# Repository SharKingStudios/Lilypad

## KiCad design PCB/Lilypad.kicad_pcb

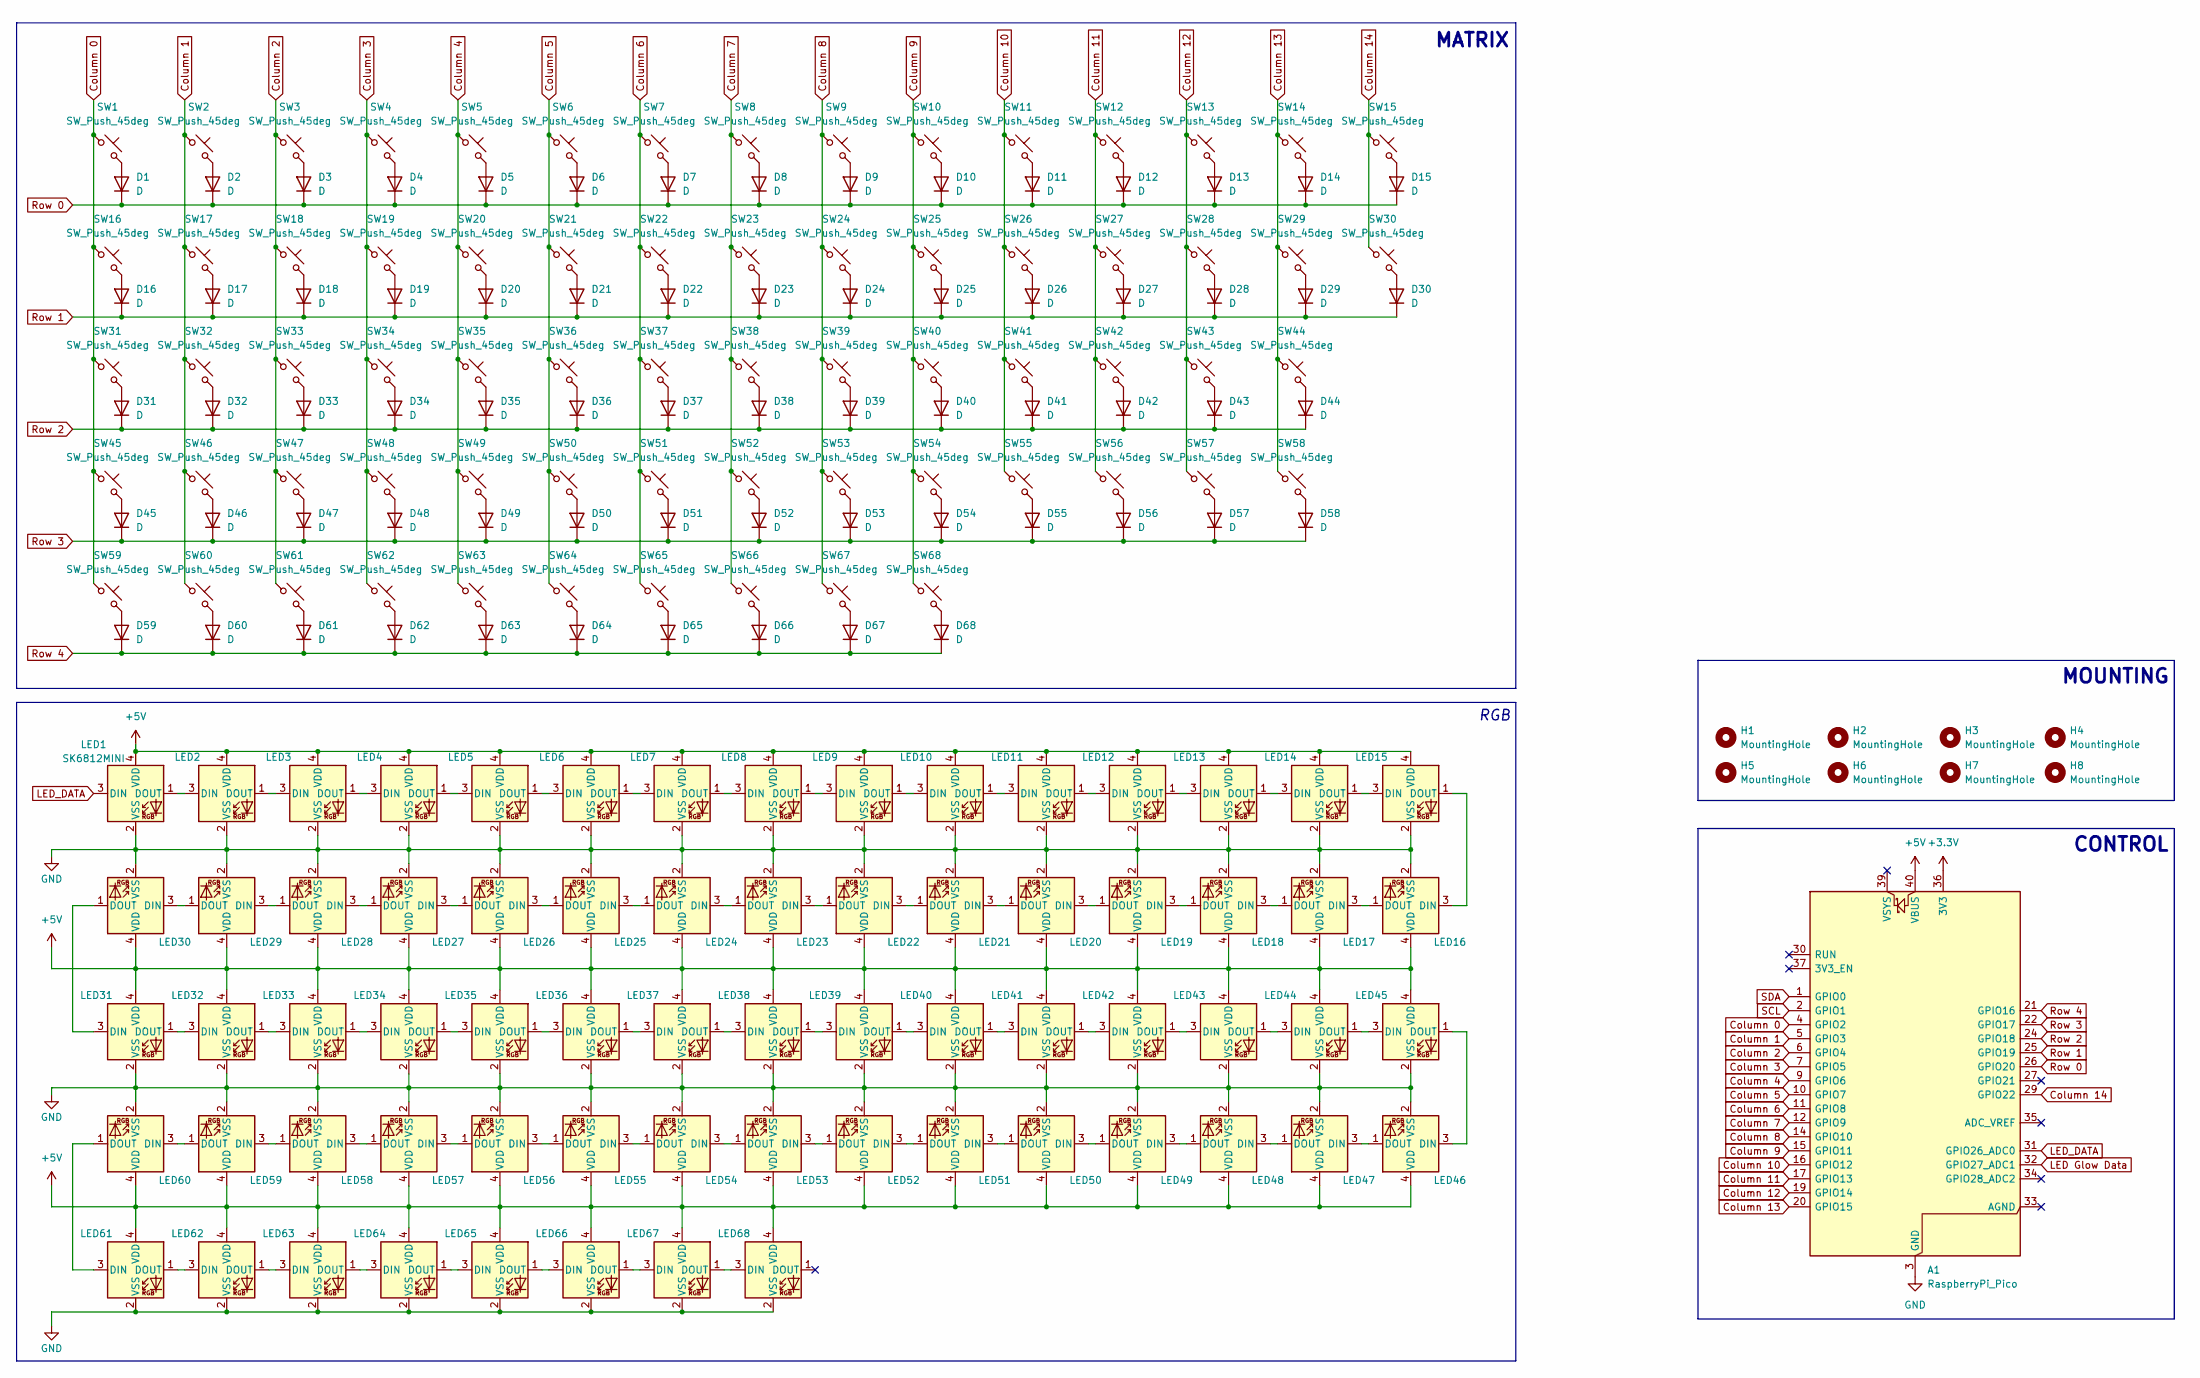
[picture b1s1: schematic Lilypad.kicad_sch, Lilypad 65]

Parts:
A1: RaspberryPi_Pico; RaspberryPi_Pico_Common_Unspecified
D1, D2, D3, D4, D5, D6, D7, D8, D9, D10, D11, D12, D13, D14, D15, D16, D17, D18, D19, D20, D21, D22, D23, D24, D25, D26, D27, D28, D29, D30, D31, D32, D33, D34, D35, D36, D37, D38, D39, D40, D41, D42, D43, D44, D45, D46, D47, D48, D49, D50, D51, D52, D53, D54, D55, D56, D57, D58, D59, D60, D61, D62, D63, D64, D65, D66, D67, D68: D; D_SOD-123F
H1, H2, H3, H4, H5, H6, H7, H8: MountingHole; MountingHole_3.2mm_M3_Pad_Via
LED1, LED2, LED3, LED4, LED5, LED6, LED7, LED8, LED9, LED10, LED11, LED12, LED13, LED14, LED15, LED16, LED17, LED18, LED19, LED20, LED21, LED22, LED23, LED24, LED25, LED26, LED27, LED28, LED29, LED30, LED31, LED32, LED33, LED34, LED35, LED36, LED37, LED38, LED39, LED40, LED41, LED42, LED43, LED44, LED45, LED46, LED47, LED48, LED49, LED50, LED51, LED52, LED53, LED54, LED55, LED56, LED57, LED58, LED59, LED60, LED61, LED62, LED63, LED64, LED65, LED66, LED67, LED68: SK6812MINI; SK6812-MINI-E
SW1, SW2, SW3, SW4, SW5, SW6, SW7, SW8, SW9, SW10, SW11, SW12, SW13, SW14, SW15, SW16, SW17, SW18, SW19, SW20, SW21, SW22, SW23, SW24, SW25, SW26, SW27, SW28, SW29, SW30, SW31, SW32, SW33, SW34, SW35, SW36, SW37, SW38, SW39, SW40, SW41, SW42, SW43, SW44, SW45, SW46, SW47, SW48, SW49, SW50, SW51, SW52, SW53, SW54, SW55, SW56, SW57, SW58, SW59, SW60, SW61, SW62, SW63, SW64, SW65, SW66, SW67, SW68: SW_Push_45deg; Kailh-PG1353-Hotswap-1U

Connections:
+3.3V: A1.36 (3V3)
+5V: A1.40 (VBUS), LED1.4 (VDD), LED2.4 (VDD), LED3.4 (VDD), LED4.4 (VDD), LED5.4 (VDD), LED6.4 (VDD), LED7.4 (VDD), LED8.4 (VDD), LED9.4 (VDD), LED10.4 (VDD), LED11.4 (VDD), LED12.4 (VDD), LED13.4 (VDD), LED14.4 (VDD), LED15.4 (VDD), LED16.4 (VDD), LED17.4 (VDD), LED18.4 (VDD), LED19.4 (VDD), LED20.4 (VDD), LED21.4 (VDD), LED22.4 (VDD), LED23.4 (VDD), LED24.4 (VDD), LED25.4 (VDD), LED26.4 (VDD), LED27.4 (VDD), LED28.4 (VDD), LED29.4 (VDD), LED30.4 (VDD), LED31.4 (VDD), LED32.4 (VDD), LED33.4 (VDD), LED34.4 (VDD), LED35.4 (VDD), LED36.4 (VDD), LED37.4 (VDD), LED38.4 (VDD), LED39.4 (VDD), LED40.4 (VDD), LED41.4 (VDD), LED42.4 (VDD), LED43.4 (VDD), LED44.4 (VDD), LED45.4 (VDD), LED46.4 (VDD), LED47.4 (VDD), LED48.4 (VDD), LED49.4 (VDD), LED50.4 (VDD), LED51.4 (VDD), LED52.4 (VDD), LED53.4 (VDD), LED54.4 (VDD), LED55.4 (VDD), LED56.4 (VDD), LED57.4 (VDD), LED58.4 (VDD), LED59.4 (VDD), LED60.4 (VDD), LED61.4 (VDD), LED62.4 (VDD), LED63.4 (VDD), LED64.4 (VDD), LED65.4 (VDD), LED66.4 (VDD), LED67.4 (VDD), LED68.4 (VDD)
Column 0: A1.4 (GPIO2), SW1.1, SW16.1, SW31.1, SW45.1, SW59.1
Column 1: A1.5 (GPIO3), SW2.1, SW17.1, SW32.1, SW46.1, SW60.1
Column 2: A1.6 (GPIO4), SW3.1, SW18.1, SW33.1, SW47.1, SW61.1; also elsewhere on the board
Column 3: A1.7 (GPIO5), SW4.1, SW19.1, SW34.1, SW48.1, SW62.1
Column 4: A1.9 (GPIO6), SW5.1, SW20.1, SW35.1, SW49.1, SW63.1
Column 5: A1.10 (GPIO7), SW6.1, SW21.1, SW36.1, SW50.1, SW64.1
Column 6: A1.11 (GPIO8), SW7.1, SW22.1, SW37.1, SW51.1, SW65.1
Column 7: A1.12 (GPIO9), SW8.1, SW23.1, SW38.1, SW52.1, SW66.1
Column 8: A1.14 (GPIO10), SW9.1, SW24.1, SW39.1, SW53.1, SW67.1
Column 9: A1.15 (GPIO11), SW10.1, SW25.1, SW40.1, SW54.1, SW68.1
Column 10: A1.16 (GPIO12), SW11.1, SW26.1, SW41.1, SW55.1
Column 11: A1.17 (GPIO13), SW12.1, SW27.1, SW42.1, SW56.1
Column 12: A1.19 (GPIO14), SW13.1, SW28.1, SW43.1, SW57.1
Column 13: A1.20 (GPIO15), SW14.1, SW29.1, SW44.1, SW58.1
Column 14: A1.29 (GPIO22), SW15.1, SW30.1
GND: A1.3 (GND), A1.8 (GND), A1.13 (GND), A1.18 (GND), A1.23 (GND), A1.28 (GND), A1.38 (GND), LED1.2 (VSS), LED2.2 (VSS), LED3.2 (VSS), LED4.2 (VSS), LED5.2 (VSS), LED6.2 (VSS), LED7.2 (VSS), LED8.2 (VSS), LED9.2 (VSS), LED10.2 (VSS), LED11.2 (VSS), LED12.2 (VSS), LED13.2 (VSS), LED14.2 (VSS), LED15.2 (VSS), LED16.2 (VSS), LED17.2 (VSS), LED18.2 (VSS), LED19.2 (VSS), LED20.2 (VSS), LED21.2 (VSS), LED22.2 (VSS), LED23.2 (VSS), LED24.2 (VSS), LED25.2 (VSS), LED26.2 (VSS), LED27.2 (VSS), LED28.2 (VSS), LED29.2 (VSS), LED30.2 (VSS), LED31.2 (VSS), LED32.2 (VSS), LED33.2 (VSS), LED34.2 (VSS), LED35.2 (VSS), LED36.2 (VSS), LED37.2 (VSS), LED38.2 (VSS), LED39.2 (VSS), LED40.2 (VSS), LED41.2 (VSS), LED42.2 (VSS), LED43.2 (VSS), LED44.2 (VSS), LED45.2 (VSS), LED46.2 (VSS), LED47.2 (VSS), LED48.2 (VSS), LED49.2 (VSS), LED50.2 (VSS), LED51.2 (VSS), LED52.2 (VSS), LED53.2 (VSS), LED54.2 (VSS), LED55.2 (VSS), LED56.2 (VSS), LED57.2 (VSS), LED58.2 (VSS), LED59.2 (VSS), LED60.2 (VSS), LED61.2 (VSS), LED62.2 (VSS), LED63.2 (VSS), LED64.2 (VSS), LED65.2 (VSS), LED66.2 (VSS), LED67.2 (VSS), LED68.2 (VSS)
LED Glow Data: A1.32 (GPIO27_ADC1)
LED_DATA: A1.31 (GPIO26_ADC0), LED1.3 (DIN)
unnamed: D1.2 (A), SW1.2
unnamed: D2.2 (A), SW2.2
unnamed: D3.2 (A), SW3.2
unnamed: D4.2 (A), SW4.2
unnamed: D5.2 (A), SW5.2
unnamed: D6.2 (A), SW6.2
unnamed: D7.2 (A), SW7.2
unnamed: D8.2 (A), SW8.2
unnamed: D9.2 (A), SW9.2
unnamed: D10.2 (A), SW10.2
unnamed: D11.2 (A), SW11.2
unnamed: D12.2 (A), SW12.2
unnamed: D13.2 (A), SW13.2
unnamed: D14.2 (A), SW14.2
unnamed: D15.2 (A), SW15.2
unnamed: D16.2 (A), SW16.2
unnamed: D17.2 (A), SW17.2
unnamed: D18.2 (A), SW18.2
unnamed: D19.2 (A), SW19.2
unnamed: D20.2 (A), SW20.2
unnamed: D21.2 (A), SW21.2
unnamed: D22.2 (A), SW22.2
unnamed: D23.2 (A), SW23.2
unnamed: D24.2 (A), SW24.2
unnamed: D25.2 (A), SW25.2
unnamed: D26.2 (A), SW26.2
unnamed: D27.2 (A), SW27.2
unnamed: D28.2 (A), SW28.2
unnamed: D29.2 (A), SW29.2
unnamed: D30.2 (A), SW30.2
unnamed: D31.2 (A), SW31.2
unnamed: D32.2 (A), SW32.2
unnamed: D33.2 (A), SW33.2
unnamed: D34.2 (A), SW34.2
unnamed: D35.2 (A), SW35.2
unnamed: D36.2 (A), SW36.2
unnamed: D37.2 (A), SW37.2
unnamed: D38.2 (A), SW38.2
unnamed: D39.2 (A), SW39.2
unnamed: D40.2 (A), SW40.2
unnamed: D41.2 (A), SW41.2
unnamed: D42.2 (A), SW42.2
unnamed: D43.2 (A), SW43.2
unnamed: D44.2 (A), SW44.2
unnamed: D45.2 (A), SW45.2
unnamed: D46.2 (A), SW46.2
unnamed 66: D47.2 (A), SW47.2; also elsewhere on the board
unnamed: D48.2 (A), SW48.2
unnamed: D49.2 (A), SW49.2
unnamed: D50.2 (A), SW50.2
unnamed: D51.2 (A), SW51.2
unnamed: D52.2 (A), SW52.2
unnamed: D53.2 (A), SW53.2
unnamed: D54.2 (A), SW54.2
unnamed: D55.2 (A), SW55.2
unnamed: D56.2 (A), SW56.2
unnamed: D57.2 (A), SW57.2
unnamed: D58.2 (A), SW58.2
unnamed: D59.2 (A), SW59.2
unnamed: D60.2 (A), SW60.2
unnamed: D61.2 (A), SW61.2
unnamed: D62.2 (A), SW62.2
unnamed: D63.2 (A), SW63.2
unnamed: D64.2 (A), SW64.2
unnamed: D65.2 (A), SW65.2
unnamed: D66.2 (A), SW66.2
unnamed: D67.2 (A), SW67.2
unnamed: D68.2 (A), SW68.2
unnamed: LED1.1 (DOUT), LED2.3 (DIN)
unnamed: LED2.1 (DOUT), LED3.3 (DIN)
unnamed: LED3.1 (DOUT), LED4.3 (DIN)
unnamed: LED4.1 (DOUT), LED5.3 (DIN)
unnamed: LED5.1 (DOUT), LED6.3 (DIN)
unnamed: LED6.1 (DOUT), LED7.3 (DIN)
unnamed: LED7.1 (DOUT), LED8.3 (DIN)
unnamed: LED8.1 (DOUT), LED9.3 (DIN)
unnamed: LED9.1 (DOUT), LED10.3 (DIN)
unnamed: LED10.1 (DOUT), LED11.3 (DIN)
unnamed: LED11.1 (DOUT), LED12.3 (DIN)
unnamed: LED12.1 (DOUT), LED13.3 (DIN)
unnamed: LED13.1 (DOUT), LED14.3 (DIN)
unnamed: LED14.1 (DOUT), LED15.3 (DIN)
unnamed: LED15.1 (DOUT), LED16.3 (DIN)
unnamed: LED16.1 (DOUT), LED17.3 (DIN)
unnamed: LED17.1 (DOUT), LED18.3 (DIN)
unnamed: LED18.1 (DOUT), LED19.3 (DIN)
unnamed: LED19.1 (DOUT), LED20.3 (DIN)
unnamed: LED20.1 (DOUT), LED21.3 (DIN)
unnamed: LED21.1 (DOUT), LED22.3 (DIN)
unnamed: LED22.1 (DOUT), LED23.3 (DIN)
unnamed: LED23.1 (DOUT), LED24.3 (DIN)
unnamed: LED24.1 (DOUT), LED25.3 (DIN)
unnamed: LED25.1 (DOUT), LED26.3 (DIN)
unnamed: LED26.1 (DOUT), LED27.3 (DIN)
unnamed: LED27.1 (DOUT), LED28.3 (DIN)
unnamed: LED28.1 (DOUT), LED29.3 (DIN)
unnamed: LED29.1 (DOUT), LED30.3 (DIN)
unnamed: LED30.1 (DOUT), LED31.3 (DIN)
unnamed: LED31.1 (DOUT), LED32.3 (DIN)
unnamed: LED32.1 (DOUT), LED33.3 (DIN)
unnamed: LED33.1 (DOUT), LED34.3 (DIN)
unnamed: LED34.1 (DOUT), LED35.3 (DIN)
unnamed: LED35.1 (DOUT), LED36.3 (DIN)
unnamed: LED36.1 (DOUT), LED37.3 (DIN)
unnamed: LED37.1 (DOUT), LED38.3 (DIN)
unnamed: LED38.1 (DOUT), LED39.3 (DIN)
unnamed: LED39.1 (DOUT), LED40.3 (DIN)
unnamed: LED40.1 (DOUT), LED41.3 (DIN)
unnamed: LED41.1 (DOUT), LED42.3 (DIN)
unnamed: LED42.1 (DOUT), LED43.3 (DIN)
unnamed: LED43.1 (DOUT), LED44.3 (DIN)
unnamed: LED44.1 (DOUT), LED45.3 (DIN)
unnamed: LED45.1 (DOUT), LED46.3 (DIN)
unnamed: LED46.1 (DOUT), LED47.3 (DIN)
unnamed: LED47.1 (DOUT), LED48.3 (DIN)
unnamed: LED48.1 (DOUT), LED49.3 (DIN)
unnamed: LED49.1 (DOUT), LED50.3 (DIN)
unnamed: LED50.1 (DOUT), LED51.3 (DIN)
unnamed: LED51.1 (DOUT), LED52.3 (DIN)
unnamed: LED52.1 (DOUT), LED53.3 (DIN)
unnamed: LED53.1 (DOUT), LED54.3 (DIN)
unnamed: LED54.1 (DOUT), LED55.3 (DIN)
unnamed: LED55.1 (DOUT), LED56.3 (DIN)
unnamed: LED56.1 (DOUT), LED57.3 (DIN)
unnamed: LED57.1 (DOUT), LED58.3 (DIN)
unnamed: LED58.1 (DOUT), LED59.3 (DIN)
unnamed: LED59.1 (DOUT), LED60.3 (DIN)
unnamed: LED60.1 (DOUT), LED61.3 (DIN)
unnamed: LED61.1 (DOUT), LED62.3 (DIN)
unnamed: LED62.1 (DOUT), LED63.3 (DIN)
unnamed: LED63.1 (DOUT), LED64.3 (DIN)
unnamed: LED64.1 (DOUT), LED65.3 (DIN)
unnamed: LED65.1 (DOUT), LED66.3 (DIN)
unnamed: LED66.1 (DOUT), LED67.3 (DIN)
unnamed: LED67.1 (DOUT), LED68.3 (DIN)
Row 0: A1.26 (GPIO20), D1.1 (K), D2.1 (K), D3.1 (K), D4.1 (K), D5.1 (K), D6.1 (K), D7.1 (K), D8.1 (K), D9.1 (K), D10.1 (K), D11.1 (K), D12.1 (K), D13.1 (K), D14.1 (K), D15.1 (K)
Row 1: A1.25 (GPIO19), D16.1 (K), D17.1 (K), D18.1 (K), D19.1 (K), D20.1 (K), D21.1 (K), D22.1 (K), D23.1 (K), D24.1 (K), D25.1 (K), D26.1 (K), D27.1 (K), D28.1 (K), D29.1 (K), D30.1 (K)
Row 2: A1.24 (GPIO18), D31.1 (K), D32.1 (K), D33.1 (K), D34.1 (K), D35.1 (K), D36.1 (K), D37.1 (K), D38.1 (K), D39.1 (K), D40.1 (K), D41.1 (K), D42.1 (K), D43.1 (K), D44.1 (K)
Row 3: A1.22 (GPIO17), D45.1 (K), D46.1 (K), D47.1 (K), D48.1 (K), D49.1 (K), D50.1 (K), D51.1 (K), D52.1 (K), D53.1 (K), D54.1 (K), D55.1 (K), D56.1 (K), D57.1 (K), D58.1 (K)
Row 4: A1.21 (GPIO16), D59.1 (K), D60.1 (K), D61.1 (K), D62.1 (K), D63.1 (K), D64.1 (K), D65.1 (K), D66.1 (K), D67.1 (K), D68.1 (K)
SCL: A1.2 (GPIO1)
SDA: A1.1 (GPIO0)

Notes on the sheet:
RGB
MOUNTING
CONTROL
MATRIX

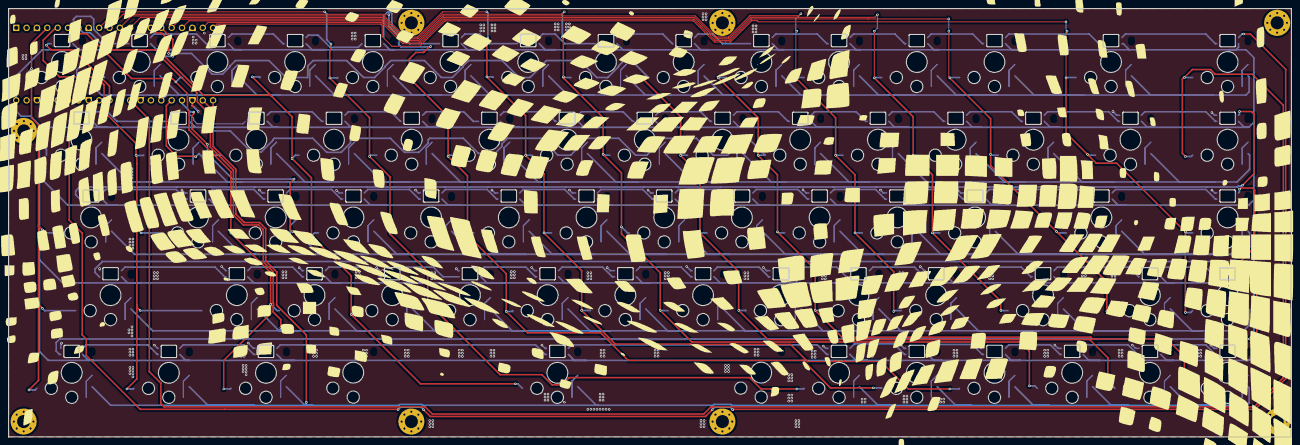
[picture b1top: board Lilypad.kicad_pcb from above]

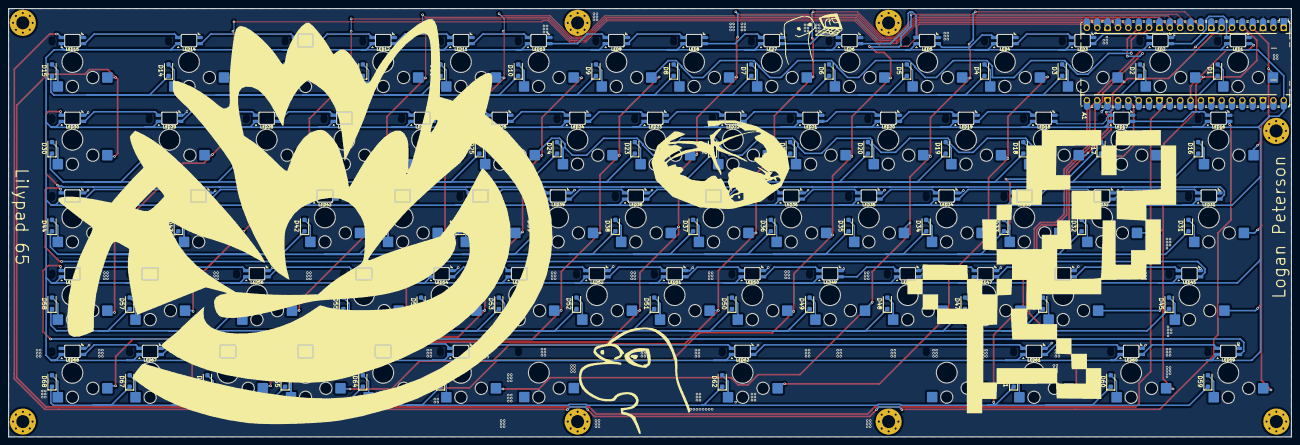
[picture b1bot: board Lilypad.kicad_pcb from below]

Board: 2 copper layers, 314.5 x 105.0 mm, 215 parts (207 on the bottom side), 158 nets.

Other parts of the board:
SW47#2, SW47#3: SW_Push_45deg; Kailh-PG1353-Hotswap-1U

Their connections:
Column 2: SW47#2.1; also elsewhere on the board
unnamed 66: SW47#2.2; also elsewhere on the board

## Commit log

2026-06-08 PCB Done
    8 hours later and we have a keeb.
